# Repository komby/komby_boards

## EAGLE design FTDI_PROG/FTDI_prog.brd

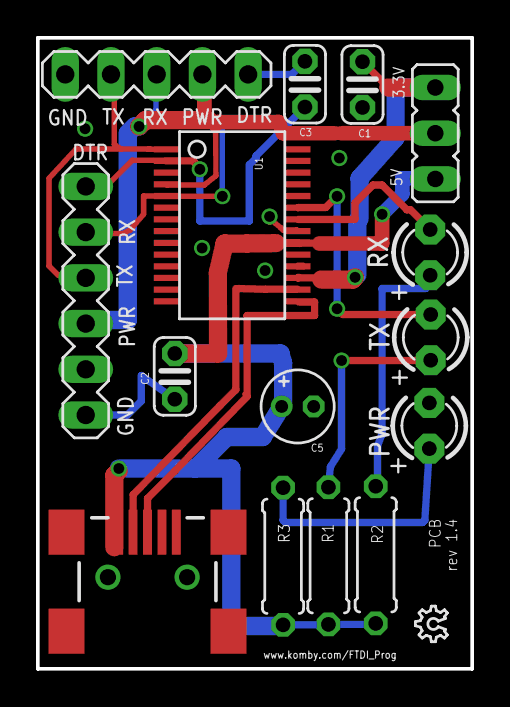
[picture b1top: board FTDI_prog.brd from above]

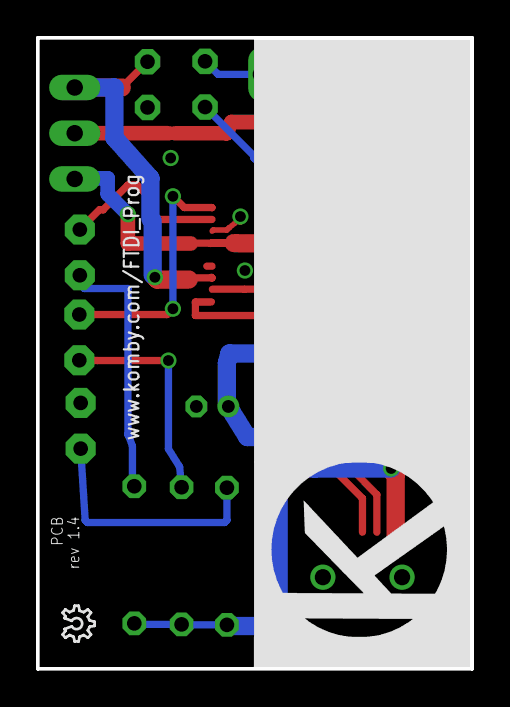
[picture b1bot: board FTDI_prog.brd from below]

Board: 2 copper layers, 24.1 x 35.1 mm, 18 parts (2 on the bottom side), 15 nets.

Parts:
C1, C2: 0.1uF; C025-024X044
C3: C025-024X044
C5: 10uF; E1,8-4
LED1: Red; LED3MM
LED2: Green; LED3MM
LED3: PWR; LED3MM
LOGO1, LOGO2: OSHW_LOGO_6MILX0070-NT; OSHW_6X70_NOTEXT
R1, R2, R3: 1K; 0207/7
SJ2: JP2
SV1: MA06-1
SV2: MA05-1
U1: FT232RLSSOP; SSOP28DB
U$2: KOMBY_LOGO_1CMX1CM
X2: USB-SMD-NS; USB-MINIB-NOSTOP

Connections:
3.3V: C1.1, SJ2.3, U1.17
5V: C2.1, C5.+, R1.2, R2.2, R3.2, SJ2.1, U1.20, X2.VBUS
DTR: C3.2, SV1.1, U1.2
GND: C1.2, C2.2, C5.-, LED3.K, SV1.6, SV2.5, U1.7, U1.18, U1.21, U1.25, U1.26, X2.GND
unnamed: LED1.A, R1.1
unnamed: LED2.A, R2.1
unnamed: LED3.A, R3.1
unnamed: C3.1, SV2.1
POWER: SJ2.2, SV1.4, SV2.2, U1.4
RXI: SV1.2, SV2.3, U1.5
RXLED: LED2.K, U1.22
TXLED: LED1.K, U1.23
TXO: SV1.3, SV2.4, U1.1
USB_D+: U1.15, X2.D+
USB_D-: U1.16, X2.D-

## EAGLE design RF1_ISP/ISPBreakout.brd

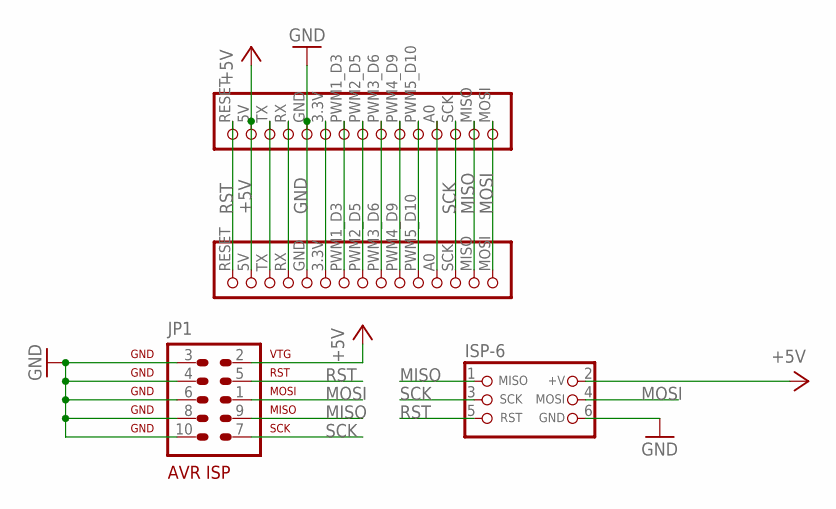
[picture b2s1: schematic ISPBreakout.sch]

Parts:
ISP-6: ISP 6; HEADER_PRG_2X03
JP1: ISP-10; AVR-ISP-10
U$1, U$2: RF1_HEADER_LEFT; RF1_LEFTHEADER_ONLY

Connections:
+5V: ISP-6.2 (+V), JP1.2, U$1.5V, U$2.5V
GND: ISP-6.6 (GND), JP1.3, JP1.4, JP1.6, JP1.8, JP1.10, U$1.GND, U$2.GND
MISO: ISP-6.1 (MISO), JP1.9, U$1.MISO, U$2.MISO
MOSI: ISP-6.4 (MOSI), JP1.1, U$1.MOSI, U$2.MOSI
unnamed: U$1.TX, U$2.TX
unnamed: U$1.RX, U$2.RX
unnamed: U$1.3.3V, U$2.3.3V
unnamed: U$1.PWM1_D3 (PWM1), U$2.PWM1_D3 (PWM1)
unnamed: U$1.PWM2_D5 (PWM2), U$2.PWM2_D5 (PWM2)
unnamed: U$1.PWM3_D6 (PWM3), U$2.PWM3_D6 (PWM3)
unnamed: U$1.PWM4_D9 (PWM4), U$2.PWM4_D9 (PWM4)
unnamed: U$1.PWM5_D10 (PWM5), U$2.PWM5_D10 (PWM5)
unnamed: U$1.A0 (PC0), U$2.A0 (PC0)
RST: ISP-6.5 (RST), JP1.5, U$1.RESET, U$2.RESET
SCK: ISP-6.3 (SCK), JP1.7, U$1.SCK, U$2.SCK

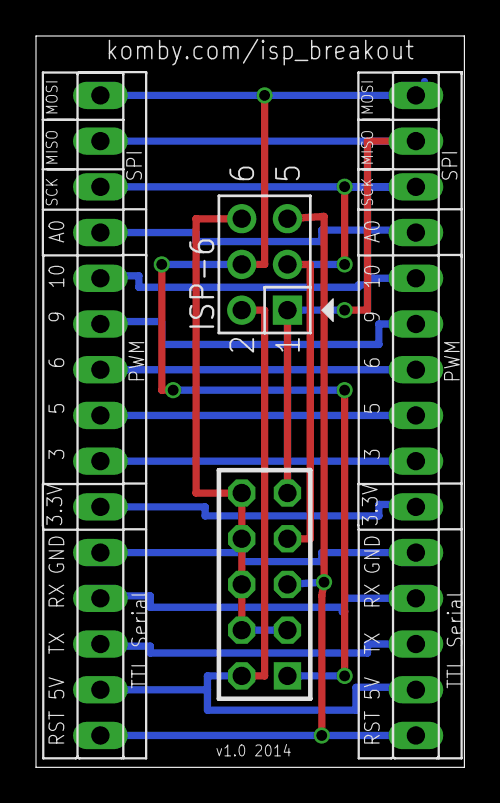
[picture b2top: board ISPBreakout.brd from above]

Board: 2 copper layers, 23.8 x 40.6 mm, 4 parts (0 on the bottom side), 15 nets.

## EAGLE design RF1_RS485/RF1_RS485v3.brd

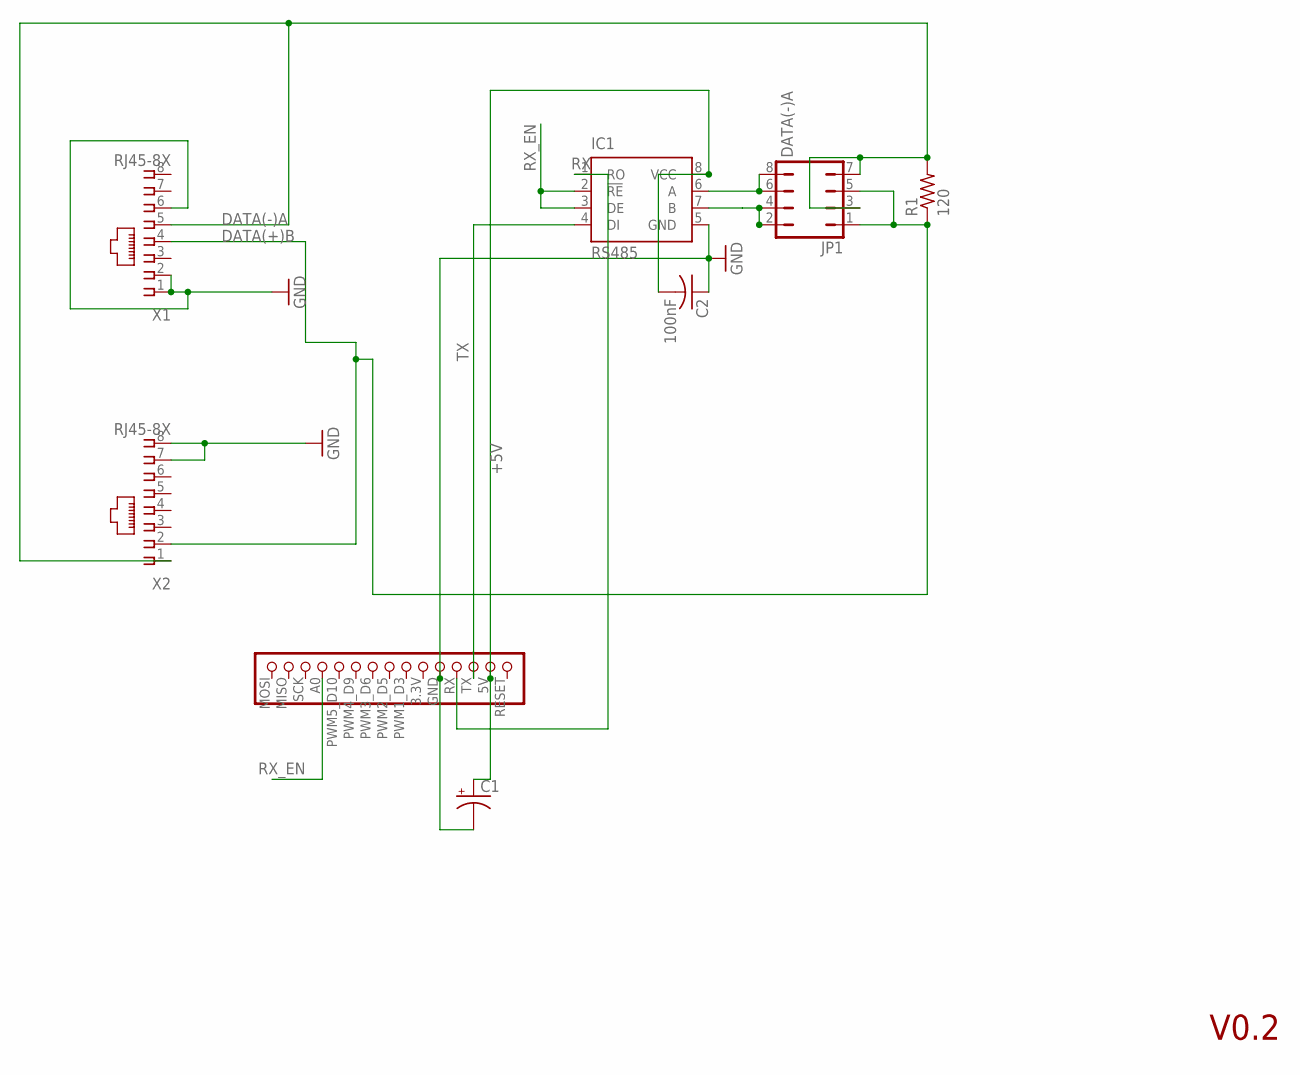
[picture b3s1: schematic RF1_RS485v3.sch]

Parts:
C1: CPOL-USE5-5; E5-5
C2: 100nF; C025-024X044
IC1: RS485; DIL08
JP1: JP4Q
R1: 120; 0805-THM
U$1: RF1_HEADER_LEFT; RF1_LEFTHEADER_ONLY
X1, X2: RJ45-8X; RJ45-NO-SHIELD

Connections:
+5V: C1.+, C2.2, IC1.8 (VCC), U$1.5V
DATA(+)B: JP1.1, JP1.5, R1.1, X1.4, X2.2
DATA(-)A: JP1.3, JP1.7, R1.2, X1.5, X2.1
GND: C1.-, C2.1, IC1.5 (GND), U$1.GND, X1.1, X1.2, X1.6, X2.7, X2.8
unnamed: IC1.6 (A), JP1.6, JP1.8
unnamed: IC1.7 (B), JP1.2, JP1.4
RX: IC1.1 (RO), U$1.RX
RX_EN: IC1.2 (!RE), IC1.3 (DE), U$1.A0 (PC0)
TX: IC1.4 (DI), U$1.TX

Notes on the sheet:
V0.2

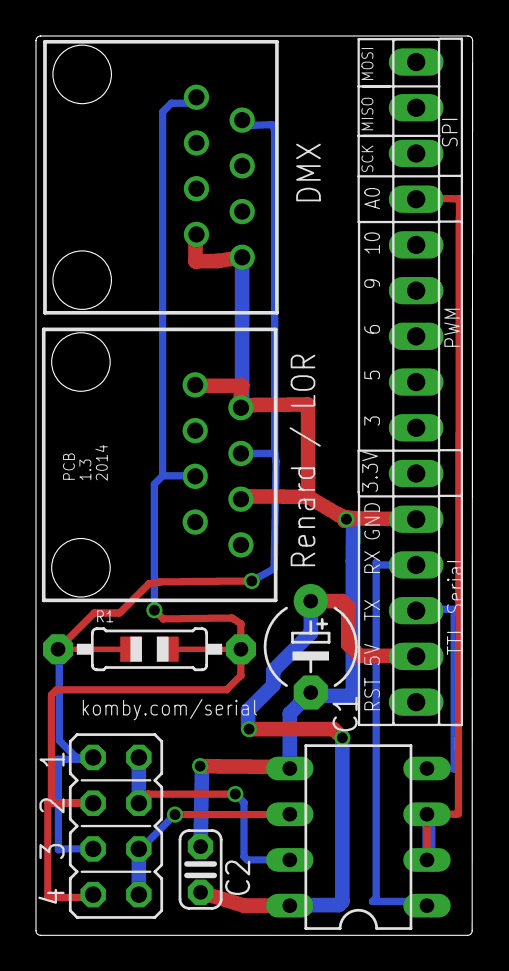
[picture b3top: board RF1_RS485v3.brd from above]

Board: 2 copper layers, 24.3 x 50.0 mm, 8 parts (0 on the bottom side), 9 nets.

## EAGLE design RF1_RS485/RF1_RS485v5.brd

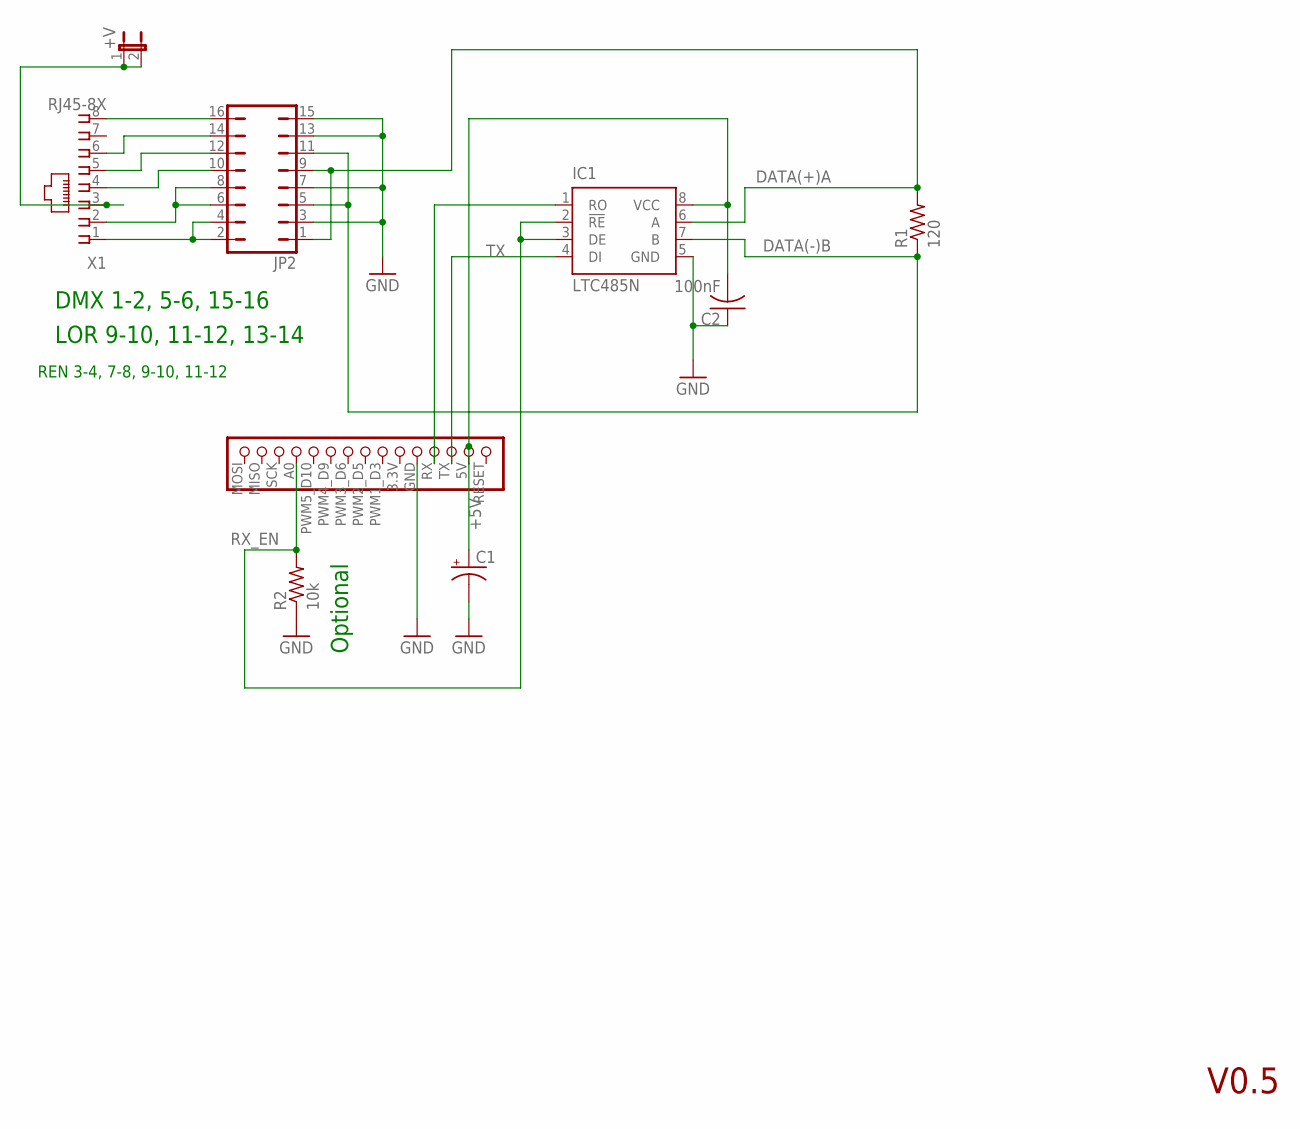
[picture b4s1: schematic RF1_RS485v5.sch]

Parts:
+V: JP1E; JP1
C1: CPOL-USE5-5; E5-5
C2: 100nF; C025-024X044
IC1: LTC485N; DIL08
JP2: JP8Q
R1: 120; 0805-THM
R2: 10k; 0805-THM
U$1: RF1_HEADER_LEFT; RF1_LEFTHEADER_ONLY
X1: RJ45-8X; RJ45-NO-SHIELD

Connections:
+5V: C1.+, C2.2, IC1.8 (VCC), U$1.5V
DATA(+)A: IC1.6 (A), JP2.1, JP2.9, R1.2
DATA(-)B: IC1.7 (B), JP2.5, JP2.11, R1.1
GND: C1.-, C2.1, IC1.5 (GND), JP2.3, JP2.7, JP2.13, JP2.15, R2.1, U$1.GND
unnamed: JP2.2, JP2.4, X1.1
unnamed: JP2.6, JP2.8, X1.2
unnamed: JP2.16, X1.8
unnamed: JP2.14, X1.6
unnamed: JP2.12, X1.5
unnamed: JP2.10, X1.4
unnamed: +V.1, +V.2, X1.3
RX: IC1.1 (RO), U$1.RX
RX_EN: IC1.2 (!RE), IC1.3 (DE), R2.2, U$1.A0 (PC0)
TX: IC1.4 (DI), U$1.TX

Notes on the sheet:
V0.5
DMX 1-2, 5-6, 15-16
LOR 9-10, 11-12, 13-14
REN 3-4, 7-8, 9-10, 11-12
Optional

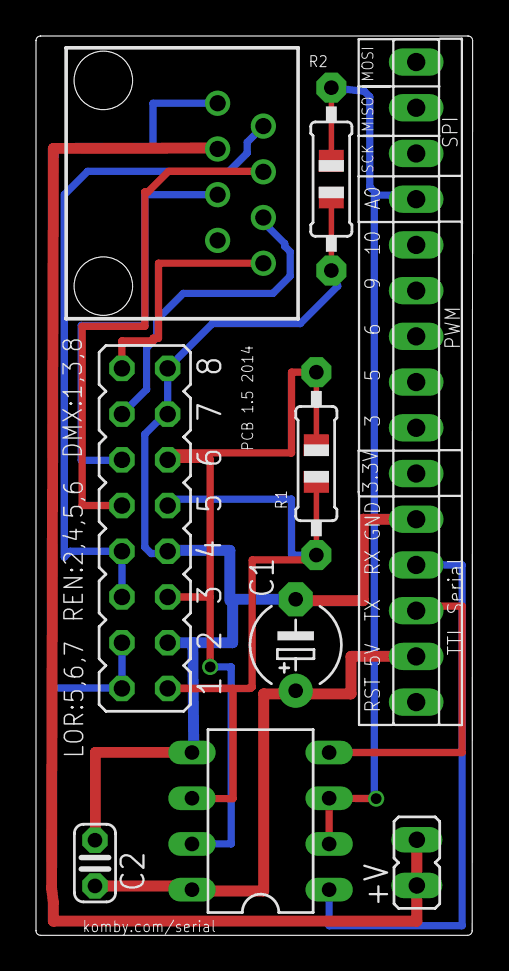
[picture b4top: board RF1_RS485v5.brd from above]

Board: 2 copper layers, 24.3 x 50.0 mm, 9 parts (0 on the bottom side), 14 nets.

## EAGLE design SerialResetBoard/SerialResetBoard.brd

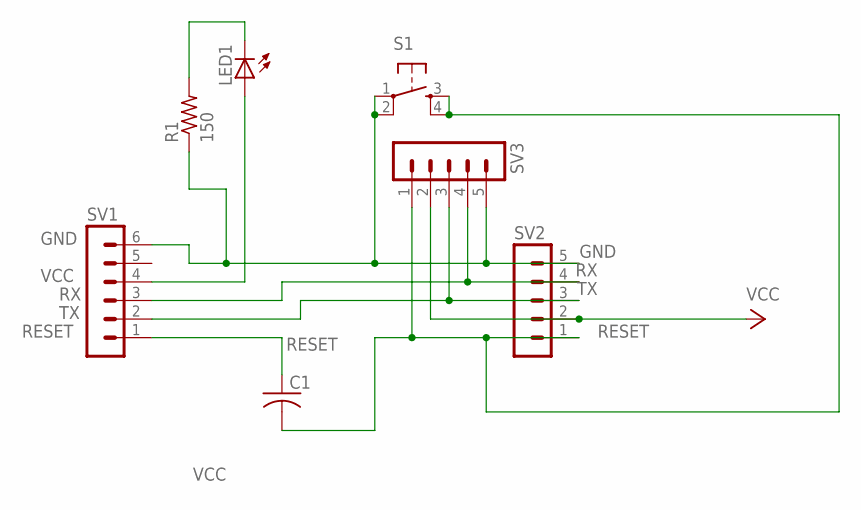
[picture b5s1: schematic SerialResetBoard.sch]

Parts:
C1: C-US025-024X044; C025-024X044
LED1: LED3MM
R1: 150; 0207/7
S1: TAC_SWITCHPTH; TACTILE-PTH
SV1: MA06-1
SV2, SV3: MA05-1

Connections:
GND: R1.1, S1.1, S1.2, SV1.6, SV2.5, SV3.5
unnamed: LED1.K (C), R1.2
unnamed: C1.1, SV1.1
RESET: C1.2, S1.3, S1.4, SV2.1, SV3.1
RX: SV1.3, SV2.4, SV3.4
TX: SV1.2, SV2.3, SV3.3
VCC: LED1.A, SV1.4, SV2.2, SV3.2

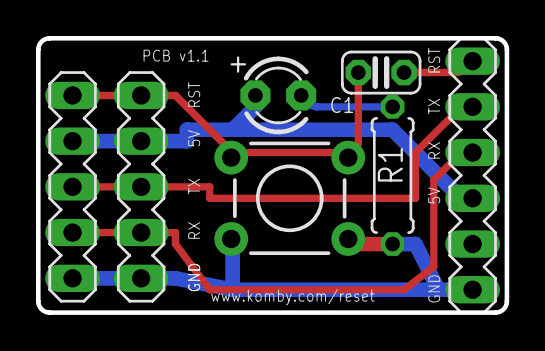
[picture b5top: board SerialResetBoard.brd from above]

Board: 2 copper layers, 26.0 x 15.2 mm, 7 parts (0 on the bottom side), 7 nets.

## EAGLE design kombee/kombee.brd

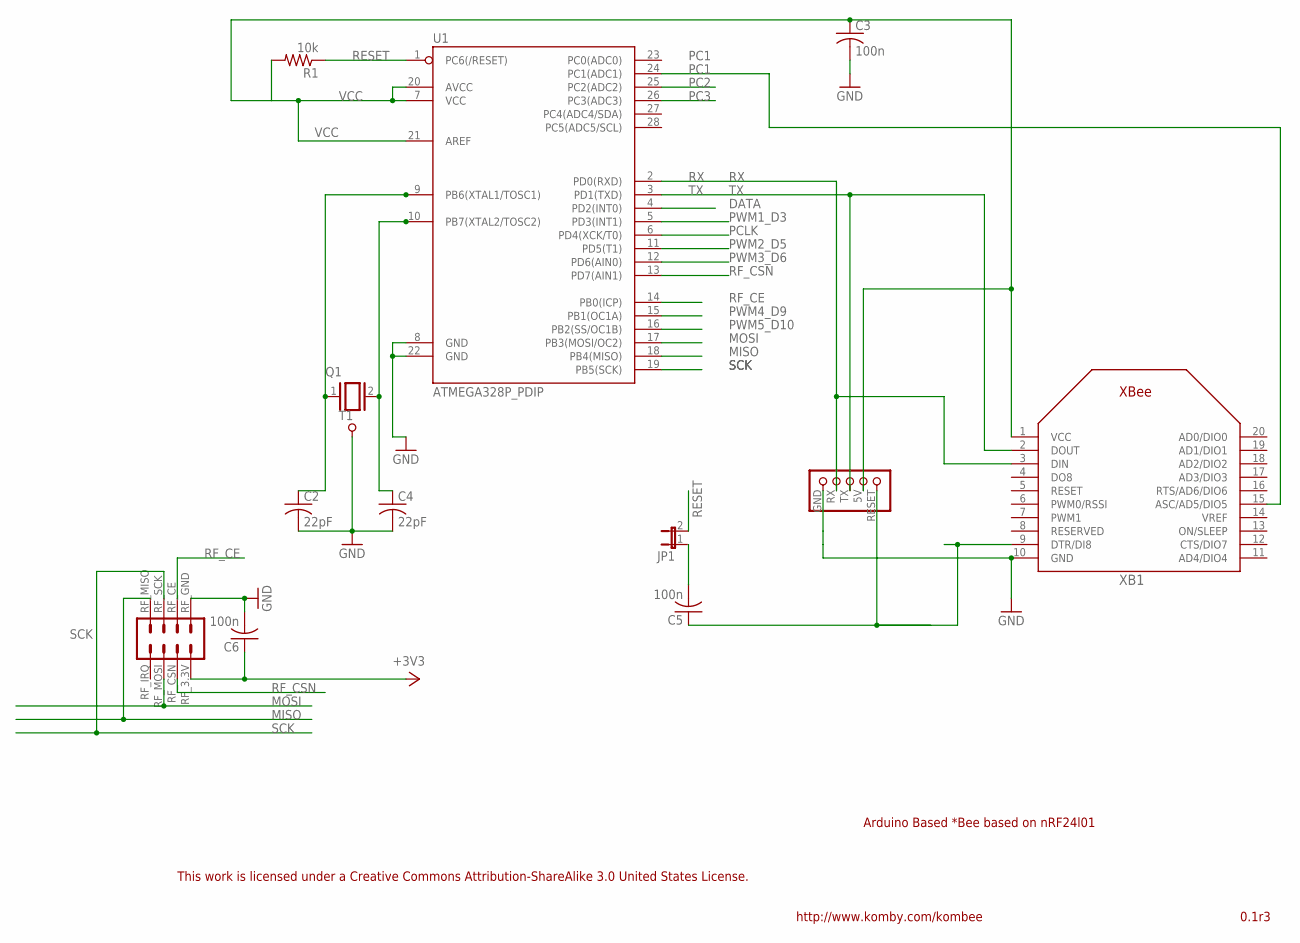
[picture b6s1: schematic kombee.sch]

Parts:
C2, C4: 22pF; C0805K
C3, C5, C6: 100n; C025-025X050
JP1: JP1E; JP1
Q1: XTAL/S; QS
R1: 10k; 0204/7
T1: PAD_TERMINAL-1.02MM_ROUND; CON_PAD_ROUND_1.02MM
U1: ATMEGA328P_PDIP; DIL28-3
U$1: NRF24L01_HEADER; NRF24L01
U$2: KOMBY_TTL_SERIAL; KOMBY_SERIAL_FOOTPRINT
XB1: XBEE

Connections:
DATA: U1.4 (PD2(INT0))
DTR: C5.1, U$2.RESET, XB1.9 (DTR/DI8)
GND: C2.2, C3.2, C4.2, C6.2, T1.P, U1.8 (GND), U1.22 (GND), U$1.RF_GND (RFGND_1), U$2.GND, XB1.10 (GND)
MISO: U1.18 (PB4(MISO)), U$1.RF_MISO
MOSI: U1.17 (PB3(MOSI/OC2)), U$1.RF_MOSI
unnamed: C4.1, Q1.2, U1.10 (PB7(XTAL2/TOSC2))
unnamed: C2.1, Q1.1, U1.9 (PB6(XTAL1/TOSC1))
unnamed: C5.2, JP1.1
PC1: U1.24 (PC1(ADC1)), XB1.15 (ASC/AD5/DIO5)
PC2: U1.25 (PC2(ADC2))
PC3: U1.26 (PC3(ADC3))
PCLK: U1.6 (PD4(XCK/T0))
PWM1_D3: U1.5 (PD3(INT1))
PWM2_D5: U1.11 (PD5(T1))
PWM3_D6: U1.12 (PD6(AIN0))
PWM4_D9: U1.15 (PB1(OC1A))
PWM5_D10: U1.16 (PB2(SS/OC1B))
RESET: JP1.2, R1.1, U1.1 (PC6(/RESET))
RF_CE: U1.14 (PB0(ICP)), U$1.RF_CE
RF_CSN: U1.13 (PD7(AIN1)), U$1.RF_CSN
RX: U1.2 (PD0(RXD)), U$2.RX, XB1.3 (DIN)
SCK: U1.19 (PB5(SCK)), U$1.RF_SCK
TX: U1.3 (PD1(TXD)), U$2.TX, XB1.2 (DOUT)
VCC: C3.1, C6.1, R1.2, U1.7 (VCC), U1.20 (AVCC), U1.21 (AREF), U$1.RF_3.3V, U$2.5V, XB1.1 (VCC)

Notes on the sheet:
Arduino Based *Bee based on nRF24l01
0.1r3
http://www.komby.com/kombee
This work is licensed under a Creative Commons Attribution-ShareAlike 3.0 United States License.

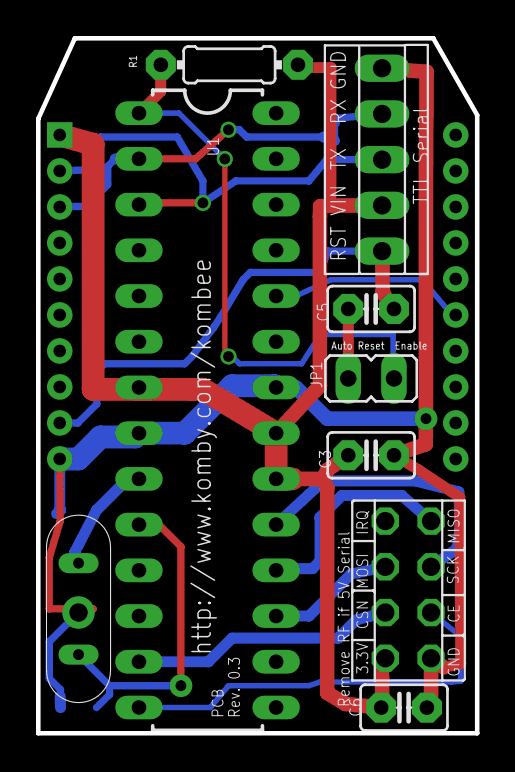
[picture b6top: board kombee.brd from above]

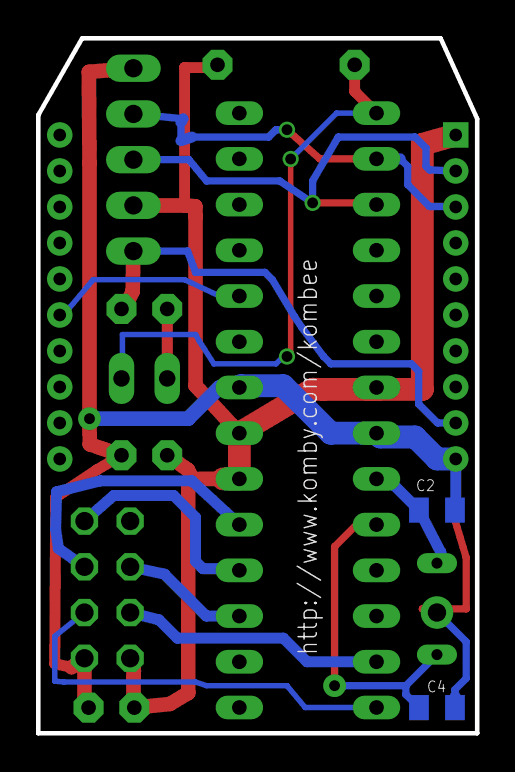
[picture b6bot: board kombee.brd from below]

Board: 2 copper layers, 24.4 x 38.6 mm, 13 parts (2 on the bottom side), 15 nets.

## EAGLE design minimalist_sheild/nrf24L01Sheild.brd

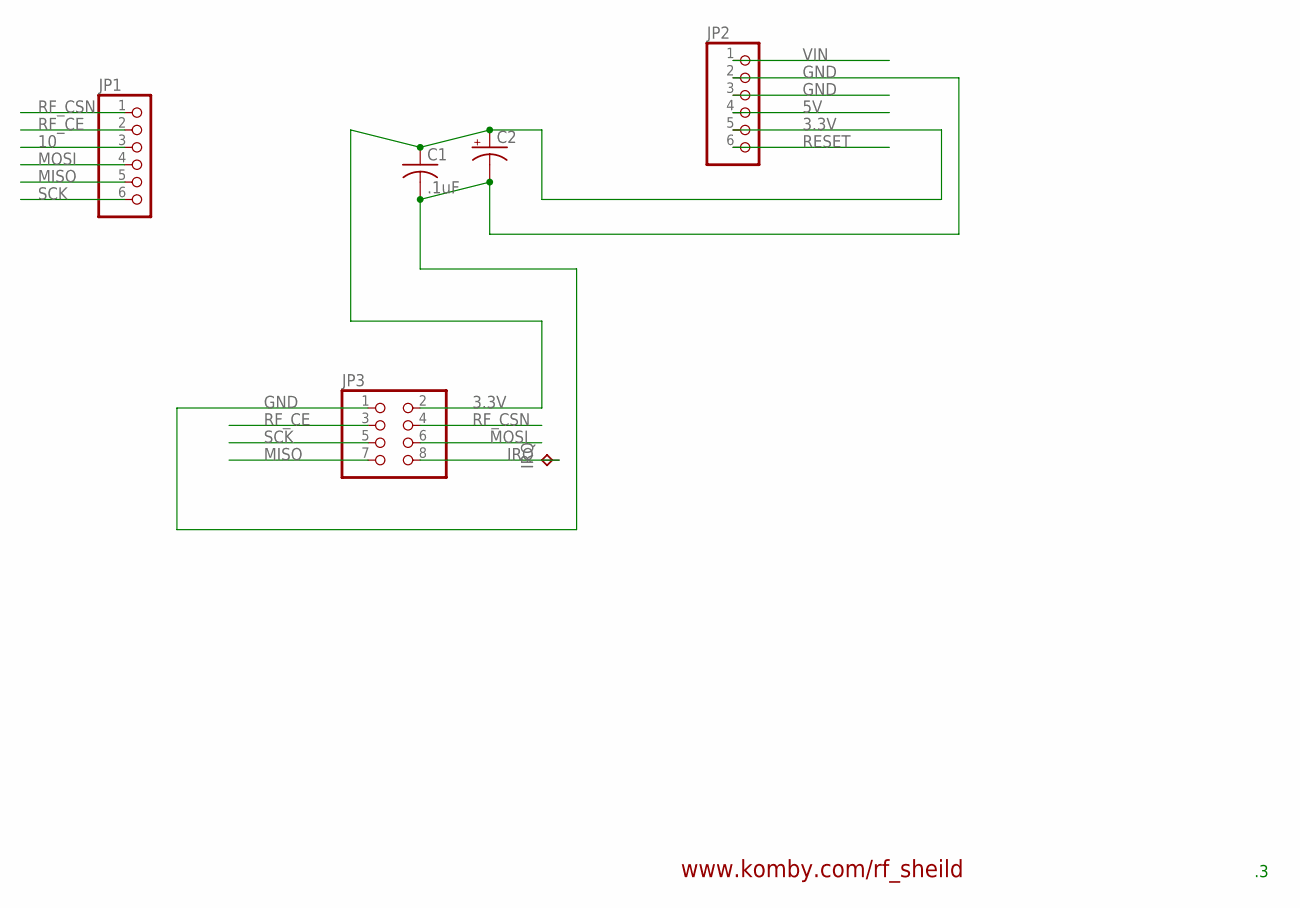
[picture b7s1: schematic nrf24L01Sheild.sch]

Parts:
C1: .1uF; C025-024X044
C2: CPOL-USE2.5-6; E2,5-6
IRQ: IRQ; P1-13
JP1, JP2: PINHD-1X6B; 1X06-BIG
JP3: PINHD-2X4; 2X04

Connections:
3.3V: C1.1, C2.+, JP2.5, JP3.2
5V: JP2.4
10: JP1.3
GND: C1.2, C2.-, JP2.2, JP2.3, JP3.1
IRQ: IRQ.TP, JP3.8
MISO: JP1.5, JP3.7
MOSI: JP1.4, JP3.6
RESET: JP2.6
RF_CE: JP1.2, JP3.3
RF_CSN: JP1.1, JP3.4
SCK: JP1.6, JP3.5
VIN: JP2.1

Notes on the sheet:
www.komby.com/rf_sheild

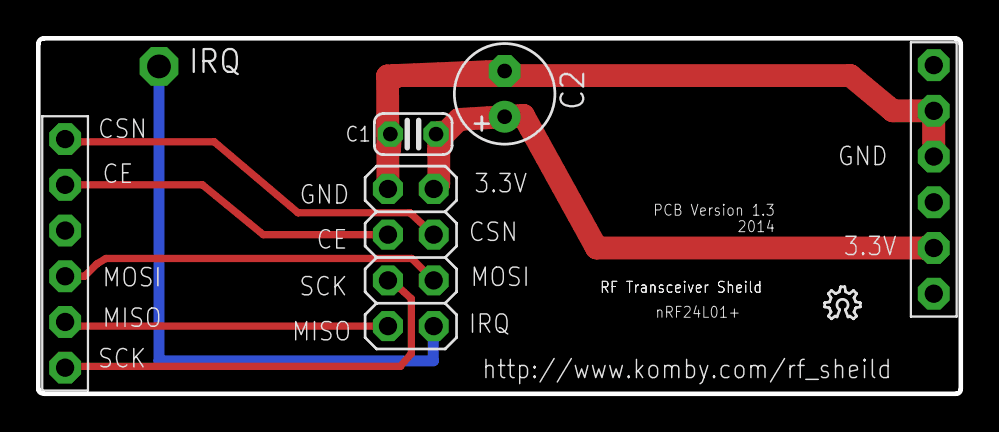
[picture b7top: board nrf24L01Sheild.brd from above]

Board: 2 copper layers, 51.2 x 19.8 mm, 7 parts (0 on the bottom side), 8 nets.

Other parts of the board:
U$1: OSHW_6X70_NOTEXT

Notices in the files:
parts and their libraries:
SparkFun-Electromechanical: Licensing: CC v3.0 Share-Alike You are welcome to use this library for commercial purposes.
